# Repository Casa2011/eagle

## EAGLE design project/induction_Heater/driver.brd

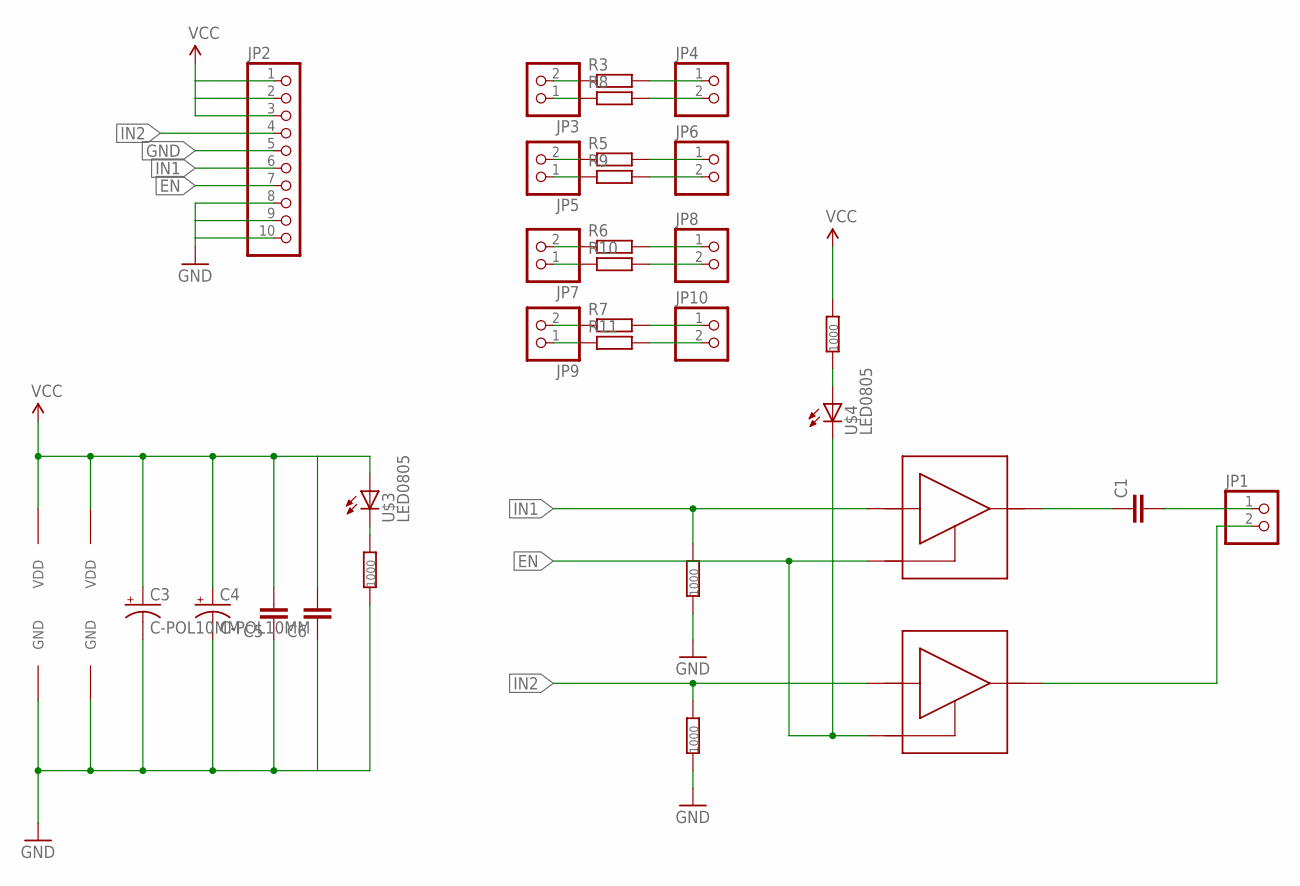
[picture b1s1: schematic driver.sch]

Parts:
C1, C5, C6: CC2220K; C2220K
C3, C4: C-POL10MM; PCAP10
JP1, JP3, JP4, JP5, JP6, JP7, JP8, JP9, JP10: PINHD-1X2; 1X02
JP2: PINHD-1X10; 1X10
R1, R2, R4, R12: 1000; R0805
R3, R5, R6, R7, R8, R9, R10, R11: R-EU_0204/7; 0204/7
U$1, U$2: IXDD614; DPACK-5
U$3, U$4: LED0805; 0805-LED

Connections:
EN: JP2.7, U$1.5 (EN), U$2.5 (EN), U$4.C
GND: C3.P$2 (-), C4.P$2 (-), C5.1, C6.1, JP2.5, JP2.8, JP2.9, JP2.10, R1.1, R2.1, R12.1, U$1.3 (GND), U$1.6 (GND), U$2.3 (GND), U$2.6 (GND)
IN1: JP2.6, R1.2, U$1.4 (IN)
IN2: JP2.4, R2.2, U$2.4 (IN)
unnamed: JP3.2, R3.1
unnamed: JP4.1, R3.2
unnamed: C1.1, U$1.2 (OUT)
unnamed: JP4.2, R8.2
unnamed: C1.2, JP1.1
unnamed: JP1.2, U$2.2 (OUT)
unnamed: JP5.2, R5.1
unnamed: JP6.1, R5.2
unnamed: JP6.2, R9.2
unnamed: JP7.2, R6.1
unnamed: JP8.1, R6.2
unnamed: JP8.2, R10.2
unnamed: JP9.2, R7.1
unnamed: JP10.1, R7.2
unnamed: JP10.2, R11.2
unnamed: JP3.1, R8.1
unnamed: JP5.1, R9.1
unnamed: JP7.1, R10.1
unnamed: JP9.1, R11.1
unnamed: R12.2, U$3.C
unnamed: R4.1, U$4.A
VCC: C3.P$1 (+), C4.P$1 (+), C5.2, C6.2, JP2.1, JP2.2, JP2.3, R4.2, U$1.1 (VDD), U$2.1 (VDD), U$3.A

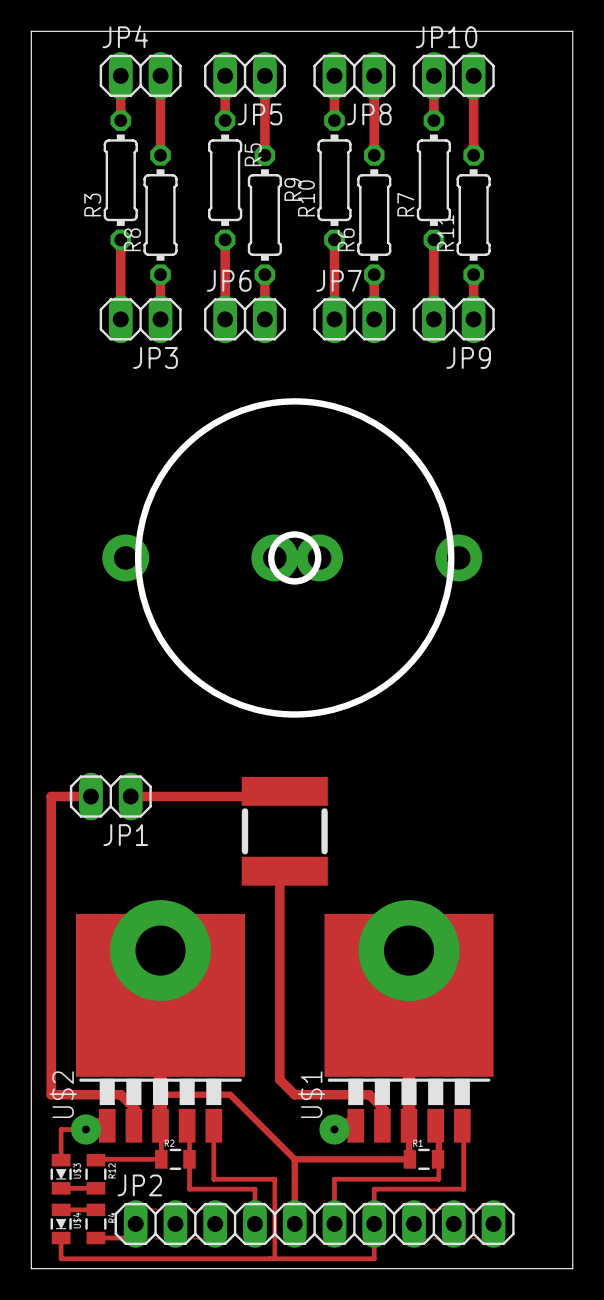
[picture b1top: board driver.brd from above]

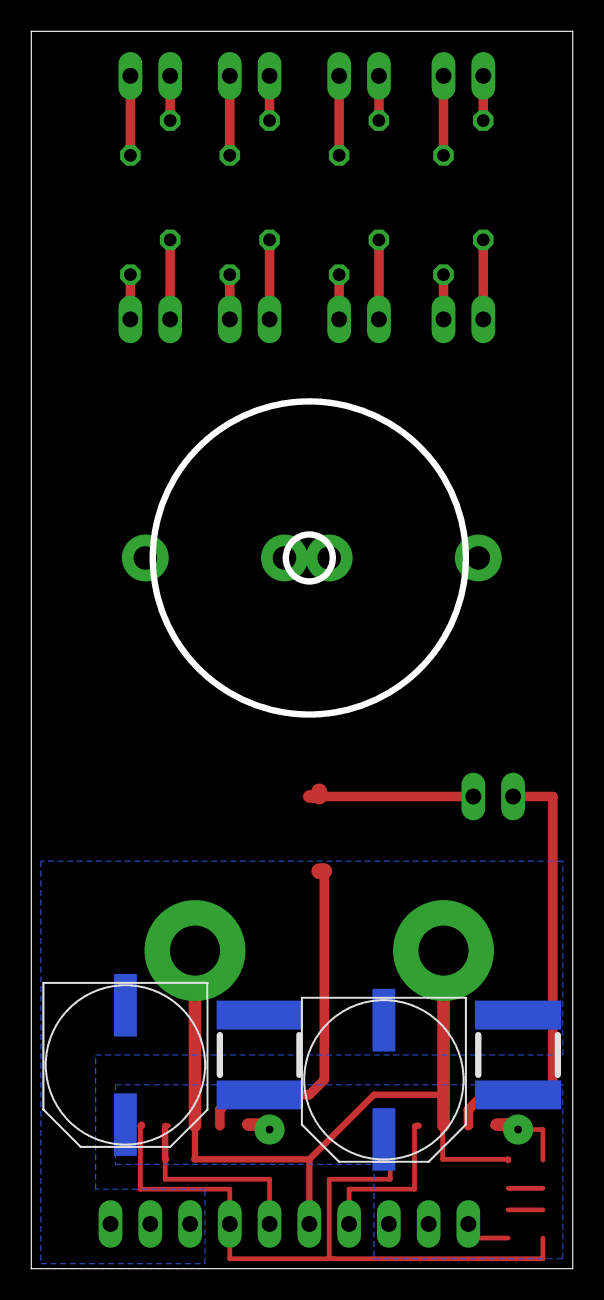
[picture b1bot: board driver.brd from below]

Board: 2 copper layers, 34.6 x 79.0 mm, 31 parts (4 on the bottom side), 26 nets.

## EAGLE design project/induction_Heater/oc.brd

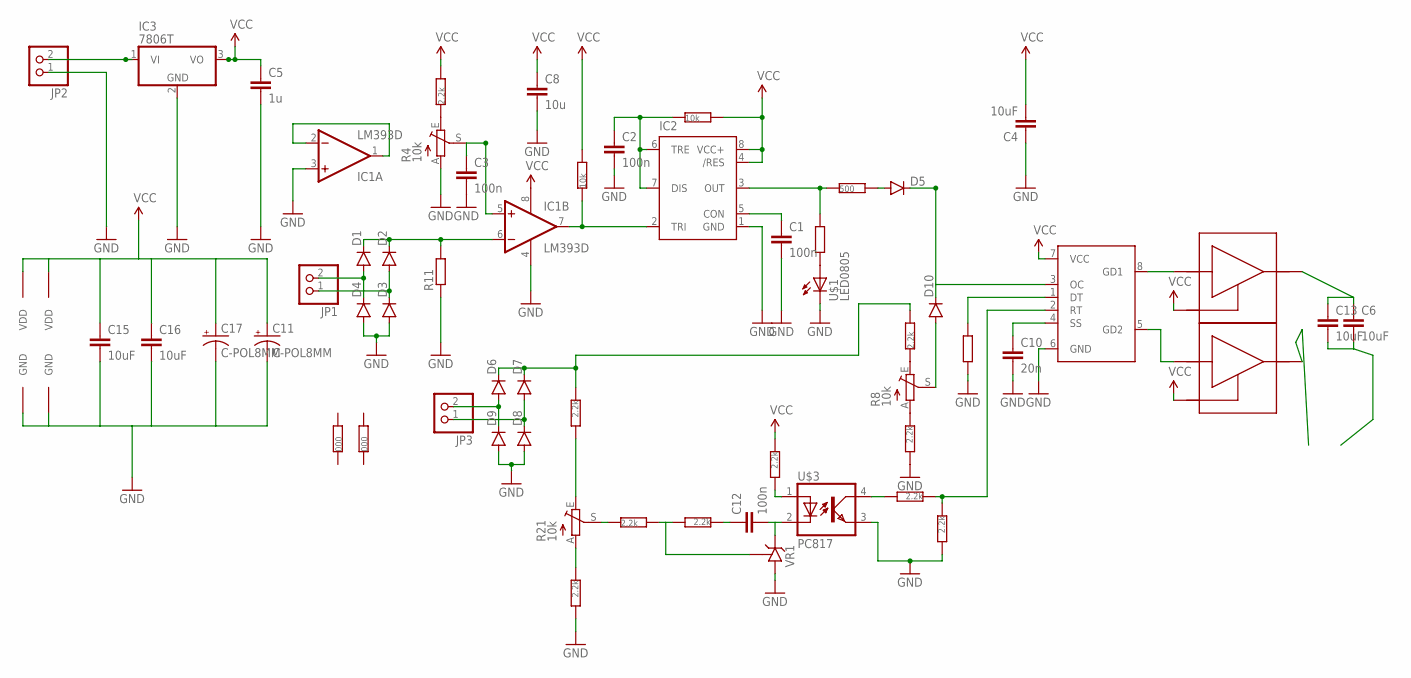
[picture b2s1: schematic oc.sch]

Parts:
C1, C2, C12: 100n; C0805
C3: 100n; C0603
C4, C6, C13, C15, C16: 10uF; 1210
C5: 1u; C0805
C8: 10u; C0805
C10: 20n; C0805
C11, C17: C-POL8MM; PCAP8
D1, D2, D3, D4, D5, D6, D7, D8, D9, D10: PMLL4150; SOD80C
IC1: LM393D; SO08
IC2: NE555D; SO08
IC3: 7806T; TO220H
JP1, JP2, JP3: PINHD-1X2; 1X02
R1, R3: 10k; R0805
R2, R6: R0805
R4, R8, R21: 10k; RJ9W
R5, R7, R12, R14, R15, R16, R17, R18, R20, R22: 2.2k; R0805
R9: 000; R1206
R10: 000; R0805
R11: R-EU_0617/17; 0617/17
R13: 500; R0805
U$1: LED0805; 0805-LED
U$2: TPS92020; SO08
U$3: PC817; DIL4-SMD
U$7, U$8: IXDD614; DPACK-5
VR1: TL431CLPSO8; SO08

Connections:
GND: C1.2, C2.2, C3.2, C4.1, C5.2, C8.2, C10.2, C11.P$2 (-), C15.2, C16.2, C17.P$2 (-), D3.A, D4.A, D8.A, D9.A, IC1.3 (+IN), IC1.4 (V-), IC2.1 (GND), IC3.2 (GND), JP2.1, R4.A, R6.1, R7.2, R11.1, R15.2, R16.2, U$1.C, U$2.6 (GND), U$3.3 (EMIT), U$7.3 (GND), U$7.6 (GND), U$8.3 (GND), U$8.6 (GND), VR1.2 (A), VR1.3 (A), VR1.6 (A), VR1.7 (A)
unnamed: D1.C, D2.C, IC1.6 (-IN), R11.2
unnamed: U$2.8 (GD1), U$8.4 (IN)
unnamed: C1.1, IC2.5 (CON)
unnamed: D5.C, D10.C, U$2.3 (OC)
unnamed: C2.1, IC2.6 (TRE), IC2.7 (DIS), R1.1
unnamed: IC2.3 (OUT), R2.2, R13.1
unnamed: R2.1, U$1.A
unnamed: IC1.7 (OUT), IC2.2 (TRI), R3.1
unnamed: R4.E, R5.1
unnamed: C3.1, IC1.5 (+IN), R4.S
unnamed: IC1.1 (OUT), IC1.2 (-IN)
unnamed: D2.A, D3.C, JP1.1
unnamed: D1.A, D4.C, JP1.2
unnamed: IC3.1 (VI), JP2.2
unnamed: U$2.5 (GD2), U$7.4 (IN)
unnamed: D5.A, R13.2
unnamed: R8.E, R12.1
unnamed: C10.1, U$2.4 (SS)
unnamed: R6.2, U$2.1 (DT)
unnamed: R14.1, R16.1, U$2.2 (RT)
unnamed: R14.2, U$3.4 (COL)
unnamed: C6.1, C13.1, U$8.2 (OUT)
unnamed: C6.2, C13.2
unnamed: D6.C, D7.C, R12.2, R20.1
unnamed: C12.2, U$3.2 (C), VR1.1 (C)
unnamed: R17.2, R18.2, VR1.8 (R)
unnamed: C12.1, R17.1
unnamed: R18.1, R21.S
unnamed: R20.2, R21.E
unnamed: D10.A, R8.S
unnamed: R22.2, U$3.1 (A)
unnamed: D7.A, D8.C, JP3.1
unnamed: D6.A, D9.C, JP3.2
unnamed: R8.A, R15.1
unnamed: R7.1, R21.A
VCC: C4.2, C5.1, C8.1, C11.P$1 (+), C15.1, C16.1, C17.P$1 (+), IC1.8 (V+), IC2.4 (/RES), IC2.8 (VCC+), IC3.3 (VO), R1.2, R3.2, R5.2, R22.1, U$2.7 (VCC), U$7.1 (VDD), U$7.5 (EN), U$8.1 (VDD), U$8.5 (EN)

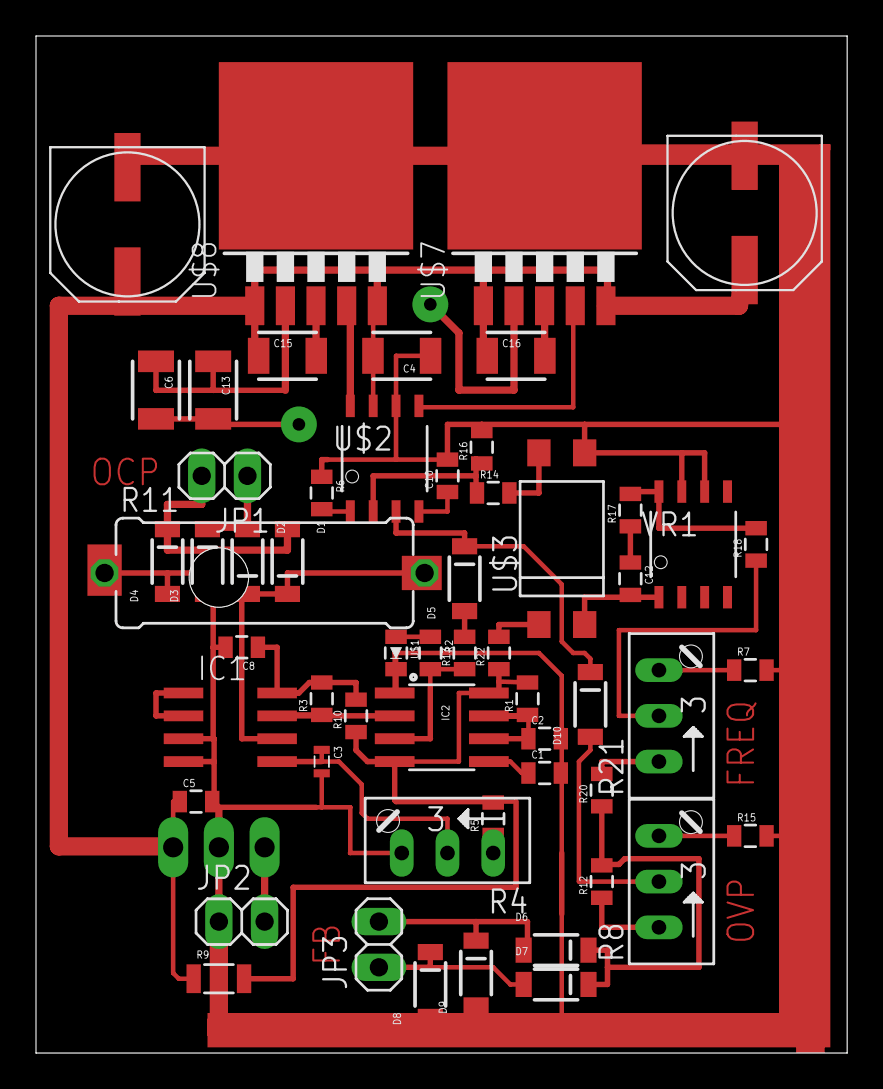
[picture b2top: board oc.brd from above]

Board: 2 copper layers, 45.1 x 56.5 mm, 58 parts (1 on the bottom side), 37 nets.

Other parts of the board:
U$4: A5P-LOC

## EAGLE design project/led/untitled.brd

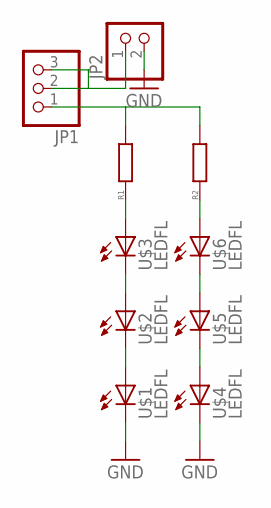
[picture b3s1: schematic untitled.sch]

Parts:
JP1: PINHD-1X03_2.54-SMD-90°; 1X03SMD/90
JP2: PINHD-1X02_2.54-SMD-90°; 1X02SMD/90
R1, R2: R0805
U$1, U$2, U$3, U$4, U$5, U$6: LEDFL; LED1

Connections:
GND: JP2.2, U$1.P$2 (C), U$4.P$2 (C)
unnamed: U$1.P$1 (A), U$2.P$2 (C)
unnamed: U$2.P$1 (A), U$3.P$2 (C)
unnamed: U$4.P$1 (A), U$5.P$2 (C)
unnamed: U$5.P$1 (A), U$6.P$2 (C)
unnamed: R1.1, U$3.P$1 (A)
unnamed: R2.1, U$6.P$1 (A)
unnamed: JP1.1, R1.2, R2.2
unnamed: JP1.2, JP1.3, JP2.1

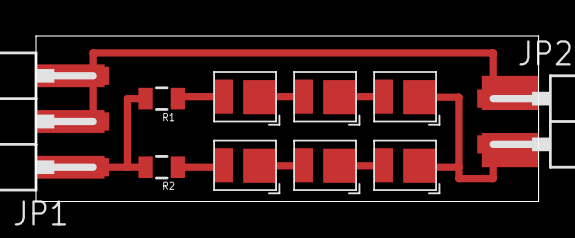
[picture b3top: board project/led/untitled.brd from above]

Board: 2 copper layers, 27.9 x 9.2 mm, 10 parts (0 on the bottom side), 9 nets.

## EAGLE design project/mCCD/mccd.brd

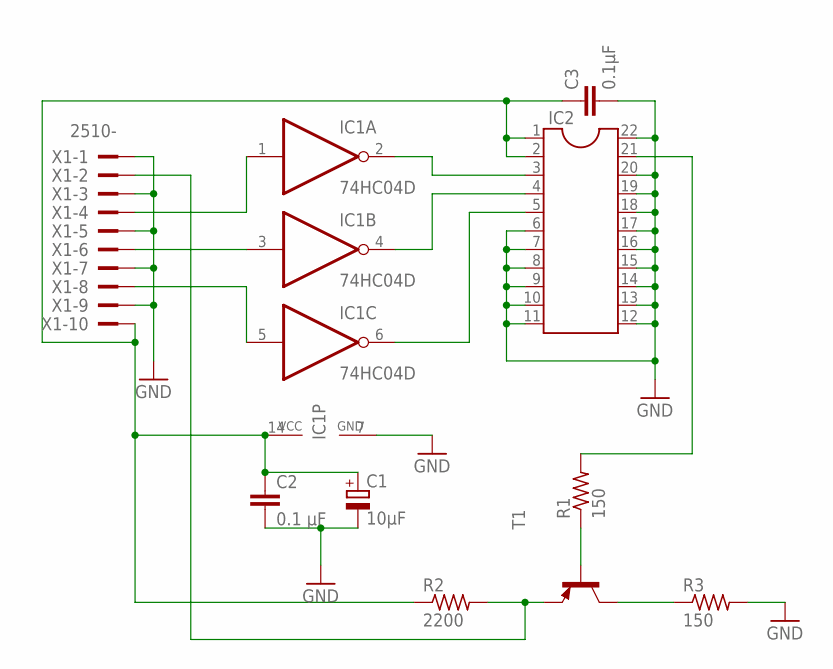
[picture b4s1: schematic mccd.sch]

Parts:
C1: 10µF; PANASONIC_D
C2: 0.1 µF; C1206
C3: 0.1µF; C1206
IC1: 74HC04D; SO14
IC2: DIL22-4
R1, R3: 150; M1206
R2: 2200; M1206
T1: -PNP-TO92-BCE; TO92-BCE
X1: 2510-; PAK100/2500-10

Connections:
GND: C1.-, C2.2, C3.2, IC1.7 (GND), IC2.6, IC2.7, IC2.8, IC2.9, IC2.10, IC2.11, IC2.12, IC2.13, IC2.14, IC2.15, IC2.16, IC2.17, IC2.18, IC2.19, IC2.20, IC2.22, R3.2, X1.1, X1.3, X1.5, X1.7, X1.9
unnamed: R2.2, T1.E, X1.2
unnamed: IC1.2 (O), IC2.3
unnamed: IC1.4 (O), IC2.4
unnamed: IC1.6 (O), IC2.5
unnamed: R3.1, T1.C
unnamed: R1.1, T1.B
unnamed: C1.+, C2.1, C3.1, IC1.14 (VCC), IC2.1, IC2.2, R2.1, X1.10
unnamed: IC2.21, R1.2
unnamed: IC1.5 (I), X1.8
unnamed: IC1.3 (I), X1.6
unnamed: IC1.1 (I), X1.4

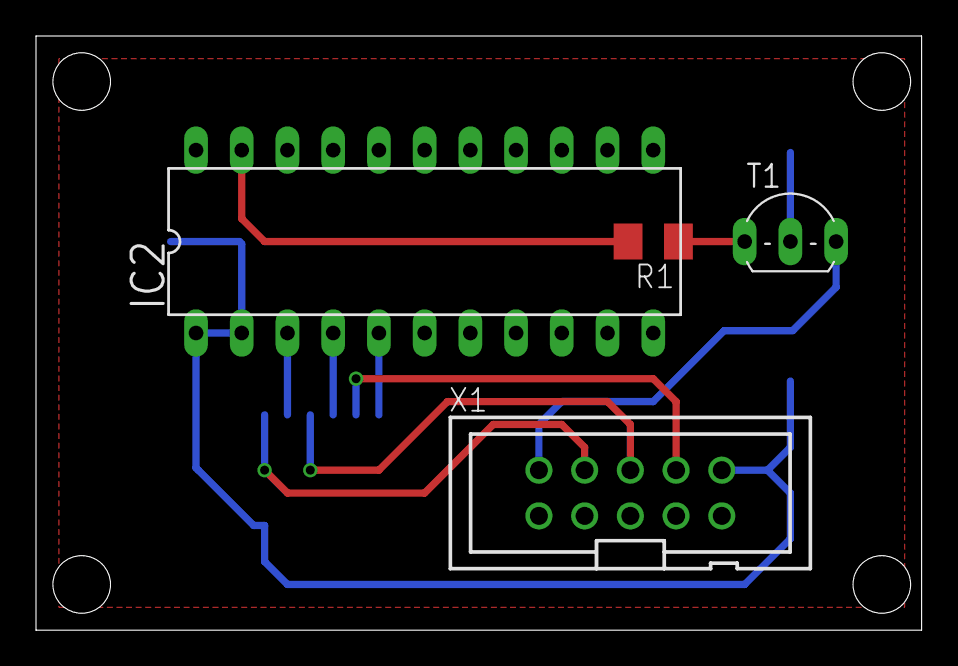
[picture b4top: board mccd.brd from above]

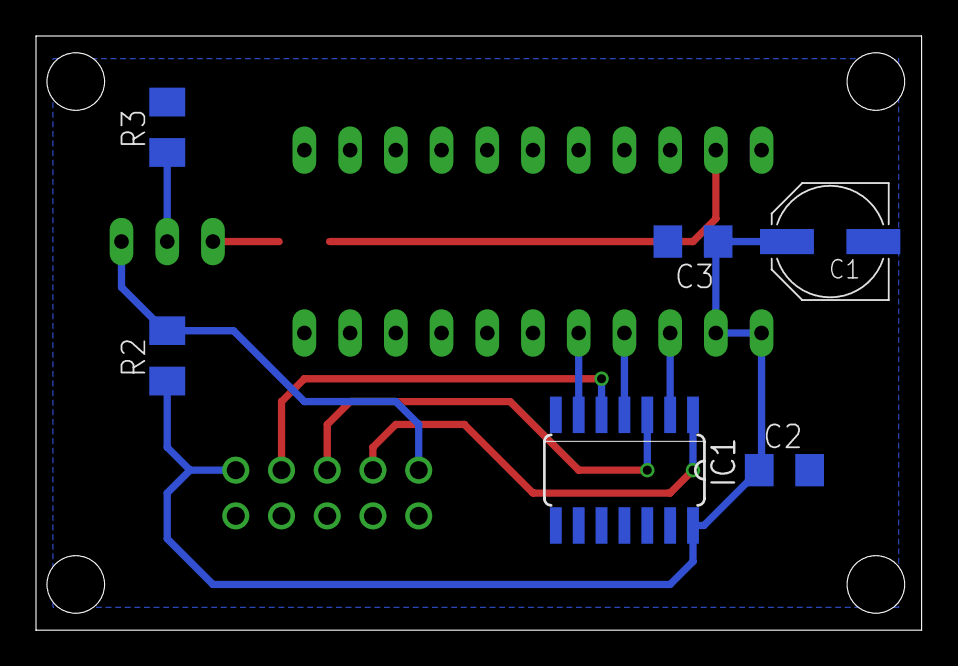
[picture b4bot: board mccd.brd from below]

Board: 2 copper layers, 49.2 x 33.0 mm, 10 parts (6 on the bottom side), 12 nets.

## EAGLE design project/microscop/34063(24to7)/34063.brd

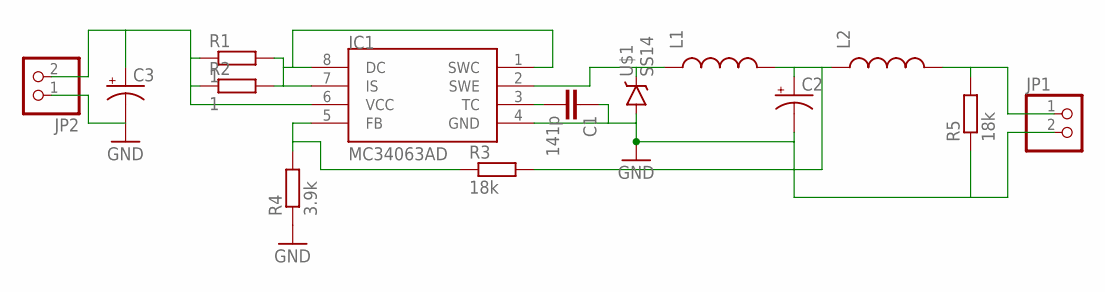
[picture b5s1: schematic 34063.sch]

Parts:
C1: 141p; C0603
C2, C3: CAP_POLE; PANASONIC_E
IC1: MC34063AD; SOIC8
JP1, JP2: PINHD-1X02_2.54; 1X02
L1: INDUCTORSRU1038; SRU1038
L2: INDUCTORVLF4012A; VLF4012A
R1, R2: 1; R0805
R3, R5: 18k; R0805
R4: 3.9k; R0805
U$1: SS14; SMA-DIODE

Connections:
GND: C1.1, C2.-, C3.-, IC1.4 (GND), JP1.2, JP2.1, R4.1, R5.1, U$1.A
unnamed: C3.+, IC1.6 (VCC), JP2.2, R1.1, R2.1
unnamed: IC1.2 (SWE), L1.1, U$1.C
unnamed: IC1.1 (SWC), IC1.7 (IS), IC1.8 (DC), R1.2, R2.2
unnamed: C2.+, L1.2, L2.P$1 (1), R3.2
unnamed: C1.2, IC1.3 (TC)
unnamed: JP1.1, L2.P$2 (2), R5.2
unnamed: IC1.5 (FB), R3.1, R4.2

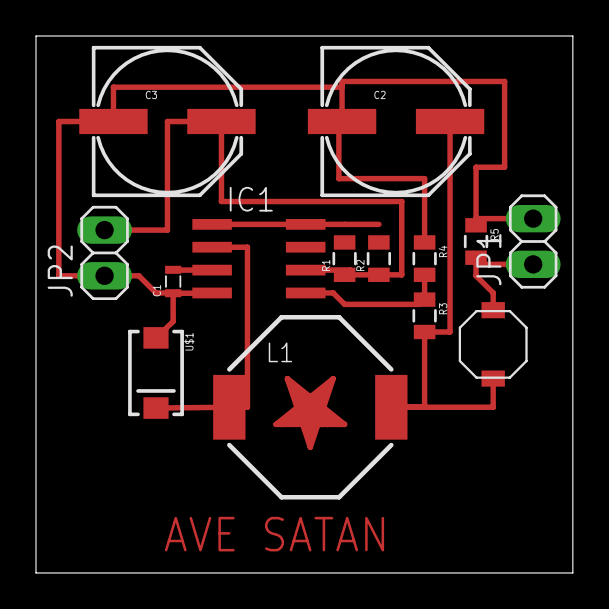
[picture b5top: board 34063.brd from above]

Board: 2 copper layers, 29.8 x 29.8 mm, 14 parts (0 on the bottom side), 8 nets.

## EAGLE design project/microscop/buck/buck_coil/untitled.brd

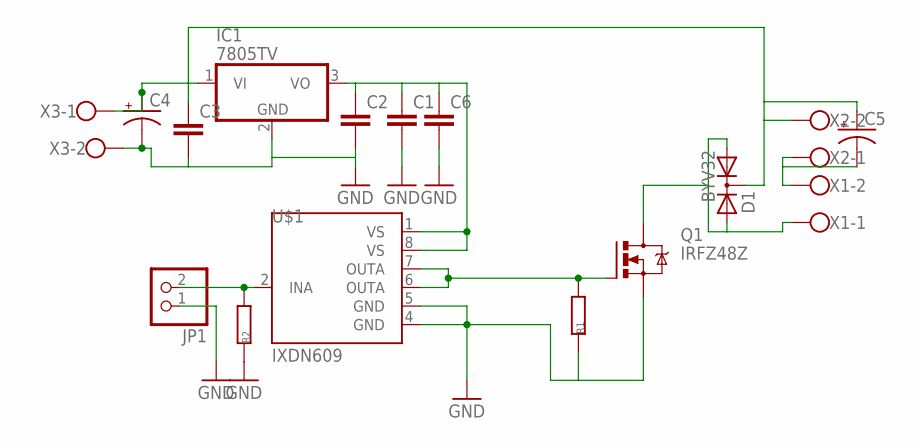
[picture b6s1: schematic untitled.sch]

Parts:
C1, C2, C3, C6: CC0805; C0805
C4, C5: CAP_POLPTH4; CPOL-RADIAL-1000UF-25V
D1: BYV32; TO220ABS
IC1: 7805TV; TO220V
JP1: PINHD-1X2; 1X02
Q1: IRFZ48Z; TO220BH
R1, R2: R0805
U$1: IXDN609; SO08
X1, X2, X3: W237-102

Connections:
GND: C1.2, C2.2, C3.2, C4.-, C6.2, IC1.2 (GND), JP1.1, Q1.S, R1.1, R2.1, U$1.4 (GND), U$1.5 (GND), X3.2
unnamed: D1.A1, D1.A2, Q1.D, X1.1
unnamed: C1.1, C2.1, C6.1, IC1.3 (VO), U$1.1 (VS), U$1.8 (VS)
unnamed: Q1.G, R1.2, U$1.6 (OUTA), U$1.7 (OUTA)
unnamed: JP1.2, R2.2, U$1.2 (INA)
unnamed: C3.1, C4.+, C5.+, D1.C, IC1.1 (VI), X2.2, X3.1
unnamed: C5.-, X1.2, X2.1

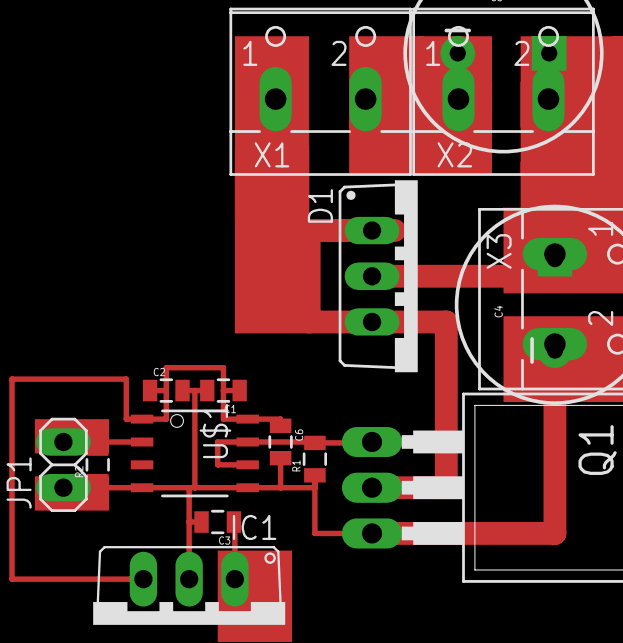
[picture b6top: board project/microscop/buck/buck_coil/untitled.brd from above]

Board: 2 copper layers, 16 parts (0 on the bottom side), 7 nets.

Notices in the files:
parts and their libraries:
SparkFun-FreqCtrl: Licensing: Creative Commons ShareAlike 4.0 International - https://creativecommons.org/licenses/by-sa/4.0
